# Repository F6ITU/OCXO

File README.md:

# OCXO
Aiôn, a 10 MHz OCXO reference

Aiôn is the god of the cyclic time in ancien Greece

This very basic and simple OCXO 10 MHz clock could be used 
as a reference for an RF generator, a frequency meter, or
any kind of equipment needing a precise timebase.

It has been originally designed to fit the "external clock input"
of any modern Software Defined Radio, Angelia being one of them

This board has been integrated in the "Alex" pcb series

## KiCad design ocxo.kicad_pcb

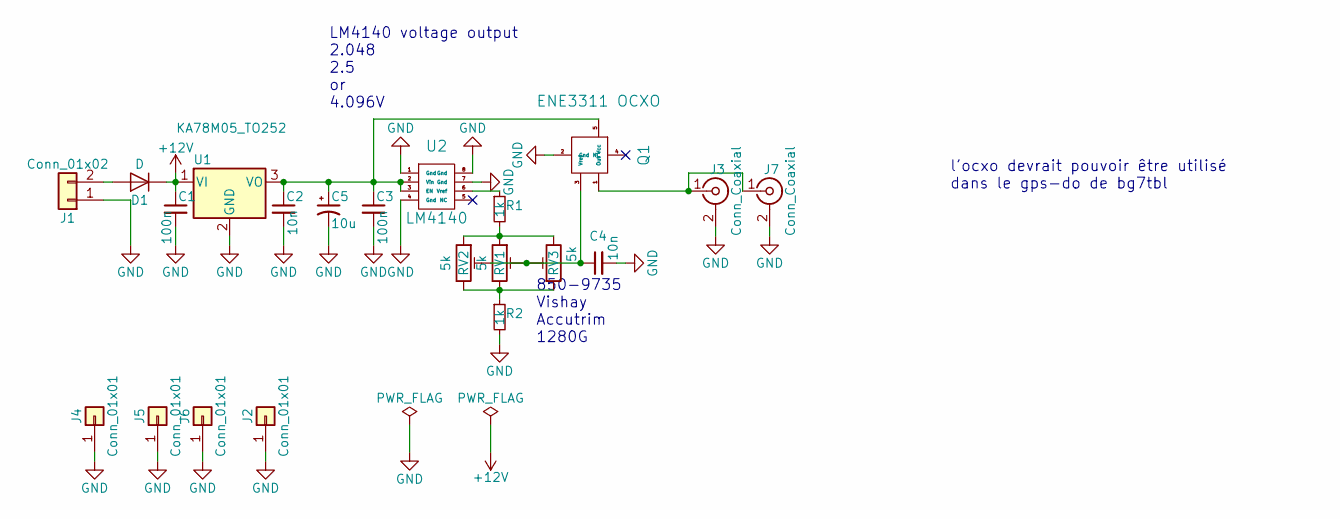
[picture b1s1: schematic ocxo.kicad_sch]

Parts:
C1, C3: 100n; C_1206_HandSoldering
C2, C4: 10n; C_0805_HandSoldering
C5: 10u; CP_Tantalum_Case-C_EIA-6032-28_Hand
D1: D; D_SMB_Handsoldering
J1: Conn_01x02; Molex_KK-6410-02_02x2.54mm_Straight
J2, J4, J5, J6: Conn_01x01; MountingHole_3.2mm_M3_ISO14580_Pad
J3: Conn_Coaxial; SMA_PINS
J7: Conn_Coaxial; SMA_EDGE_NRW
Q1: ENE3311 OCXO; ENE3311
R1, R2: 1k; R_0805_HandSoldering
RV1: 5k; Potentiometer_Trimmer_Vishay_43
RV2: 5k; Potentiometer_Trimmer_Bourns_3299Y
RV3: 5k; Potentiometer_Trimmer_Bourns_3299W
U1: KA78M05_TO252; TO-252-2Lead
U2: LM4140; SOIC-8-N

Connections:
+12V: C1.1, D1.1 (K), U1.1 (VI)
GND: C1.2, C2.2, C3.2, C4.2, C5.2, J1.1, J2.1, J3.2 (Ext), J4.1, J5.1, J6.1, J7.2 (Ext), Q1.2 (Gnd), R2.2, U1.2 (GND), U2.1 (Gnd), U2.4 (Gnd), U2.7 (Gnd), U2.8 (Gnd); also elsewhere on the board
unnamed: C2.1, C3.1, C5.1, Q1.5 (Vcc), U1.3 (VO), U2.2 (Vin), U2.3 (EN)
unnamed: C4.1, Q1.3 (Vref), RV1.2, RV2.2, RV3.2
unnamed: D1.2 (A), J1.2
unnamed: J3.1 (In), J7.1 (In), Q1.1 (Out)
unnamed: R1.1, U2.6 (Vref)
unnamed: R1.2, RV1.1, RV2.1, RV3.3
unnamed: R2.1, RV1.3, RV2.3, RV3.1

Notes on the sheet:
LM4140 voltage output 2.048 2.5 or 4.096V
850-9735 Vishay Accutrim 1280G
l'ocxo devrait pouvoir être utilisé dans le gps-do de bg7tbl

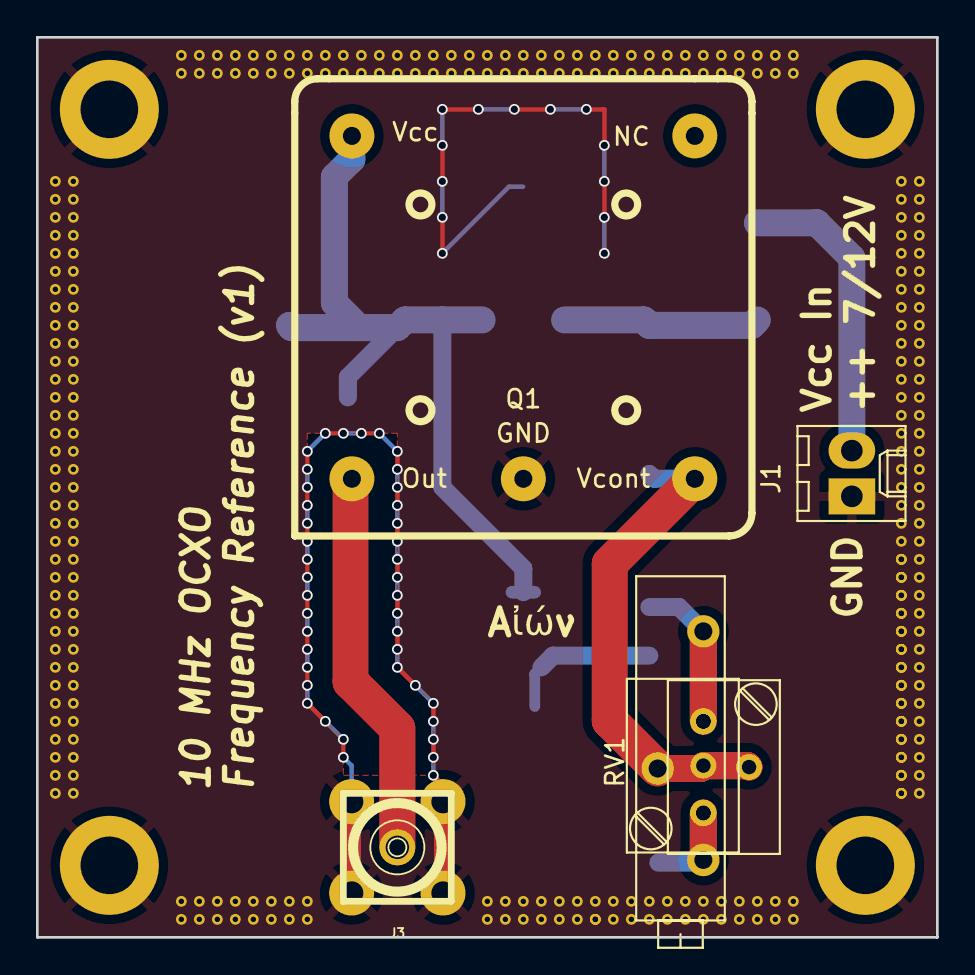
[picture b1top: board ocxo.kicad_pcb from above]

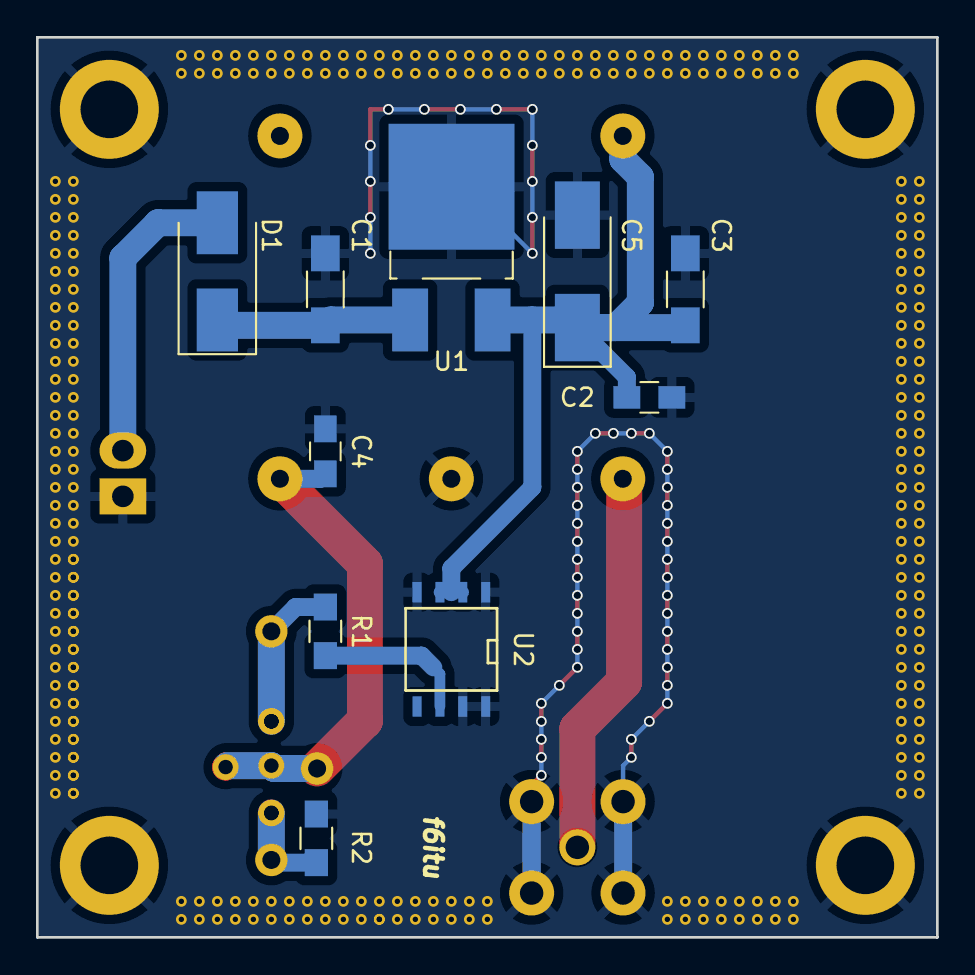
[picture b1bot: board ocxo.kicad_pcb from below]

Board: 2 copper layers, 50.0 x 50.0 mm, 20 parts (10 on the bottom side), 9 nets.

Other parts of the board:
J2#2: Conn_01x01; MountingHole_3.2mm_M3_ISO14580_Pad

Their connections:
GND: J2#2.1; also elsewhere on the board

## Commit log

2017-12-26 first draft of the OCXO
2017-12-26 adding OCXO 3D model, 3D screen captures
2017-12-31 BOM & Gerber added
2018-01-05 via stitching added, new gerber
2018-01-10 new gerber, minor changes on the output stripline
2018-02-25 minor bug fixed
2018-02-25 OCXO pad changed
2018-02-27 added output voltage for LM4140
2018-02-27 lm4140 voltage info added, tnkx to PT9KK
2019-02-15 sma cleaning
2019-03-15 upgrade to Kicad 5.x
2021-12-09 small mods on stitching
2025-01-27 gerber checked
2025-02-01 new iBom
